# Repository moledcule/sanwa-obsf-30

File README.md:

# Moledcule Sanwa OBSF 30 LED PCB

This repository contains the design and firmware for the WS2812B Programmable LED PCB for Sanwa OBSF 30mm Buttons. This PCB is designed to fit into Sanwa OBSF 30 buttons and provides customizable LED lighting effects using WS2812B LEDs.

## Table of Contents

- [Overview](#overview)
- [Features](#features)
- [Requirements](#requirements)
- [Installation](#installation)
- [Usage](#usage)
- [Contributing](#contributing)
- [License](#license)

## Overview

The Moledcule Sanwa OBSF 30 LED PCB is designed to enhance the visual appeal of your fightstick by integrating programmable WS2812B LEDs into Sanwa OBSF 30mm buttons. This PCB allows for dynamic and customizable lighting effects, adding a new dimension to your gaming experience.

## Features

- Compatible with Sanwa OBSF 30mm buttons
- Integrated WS2812B LEDs for vibrant lighting effects
- Easy installation and setup
- Customizable through firmware updates
- Low power consumption

## Requirements

- Moledcule Sanwa OBSF 30 LED PCB
- Sanwa OBSF 30mm buttons
- Power source (typically 5V via USB)
- Microcontroller (e.g., Arduino, ESP8266, ESP32) for controlling the LEDs
- Required libraries and dependencies

## Installation

1. **Hardware Setup:**
   - Install the Moledcule Sanwa OBSF 30 LED PCB into your Sanwa OBSF 30mm buttons.
   - Connect the PCB to a power source.
   - Connect the data line of the WS2812B LEDs to the microcontroller.

2. **Software Setup:**
   - Clone the repository:

     ```bash
     git clone https://github.com/moledcule/board.git
     cd board
     ```

   - Install the necessary libraries for your microcontroller. For example, if using an Arduino:

     ```bash
     arduino-cli lib install "Adafruit NeoPixel"
     ```

   - Upload the provided firmware to your microcontroller.

## Usage

1. Power on your fightstick with the Moledcule Sanwa OBSF 30 LED PCB installed.
2. The LEDs should light up according to the default configuration.
3. Customize the lighting effects by modifying the firmware and re-uploading it to the microcontroller.

## Contributing

We welcome contributions to the Moledcule Sanwa OBSF 30 LED PCB project. To contribute:

1. Fork the repository.
2. Create a new branch for your feature or bug fix.
3. Make your changes and commit them with descriptive messages.
4. Push your changes to your fork.
5. Create a pull request to the main repository.

## License

This project is licensed under the MIT License. See the [LICENSE](LICENSE) file for details.

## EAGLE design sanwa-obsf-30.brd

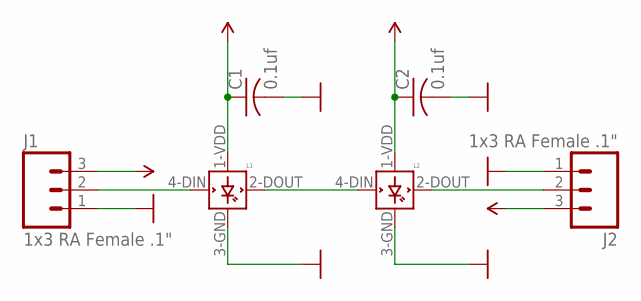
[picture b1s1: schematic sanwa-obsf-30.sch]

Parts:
C1, C2: 0.1uf; C0603K
J1, J2: 1x3 RA Female .1"; JST-3-PTH-VERT
L1, L2: WS2812B

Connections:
DATA: L1.2-DOUT (DOUT), L2.4-DIN (DIN)
DIN: J1.2, L1.4-DIN (DIN)
DOUT: J2.2, L2.2-DOUT (DOUT)
GND: C1.2, C2.2, J1.1, J2.1, L1.3-GND (GND), L2.3-GND (GND)
VCC: C1.1, C2.1, J1.3, J2.3, L1.1-VDD (VDD), L2.1-VDD (VDD)

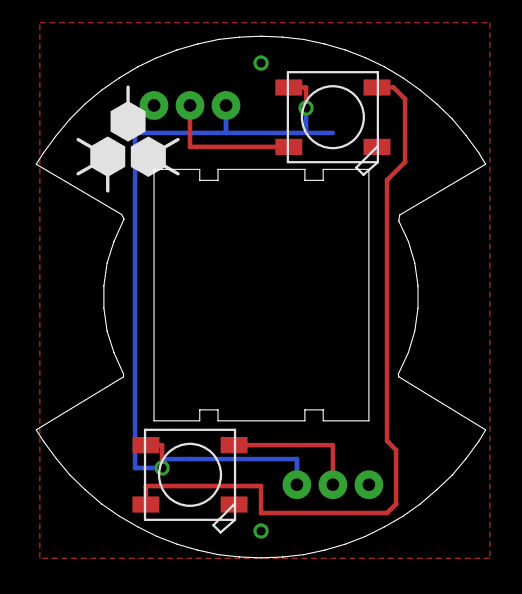
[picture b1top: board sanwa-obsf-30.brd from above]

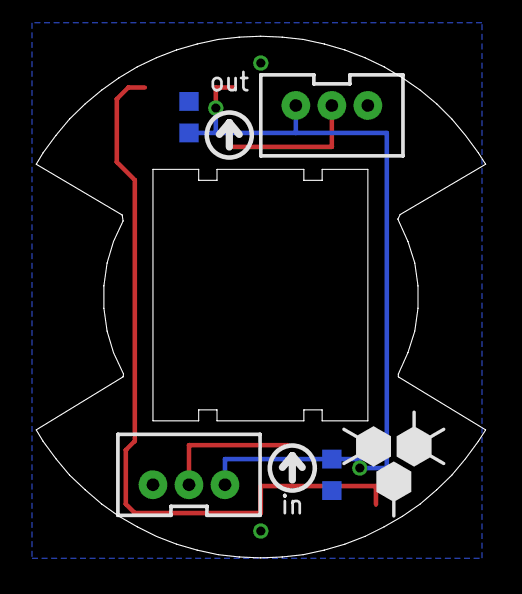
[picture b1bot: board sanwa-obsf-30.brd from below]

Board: 2 copper layers, 25.0 x 29.0 mm, 6 parts (4 on the bottom side), 5 nets.

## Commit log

2019-09-09 Mon 9 Sep 2019 10:53:03 EDT - Split Sanwa Button from original 'Moledcule' Organization
2024-07-25 README.md

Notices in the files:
parts and their libraries:
SparkFun-Connectors: Licensing: Creative Commons ShareAlike 4.0 International - https://creativecommons.org/licenses/by-sa/4.0
